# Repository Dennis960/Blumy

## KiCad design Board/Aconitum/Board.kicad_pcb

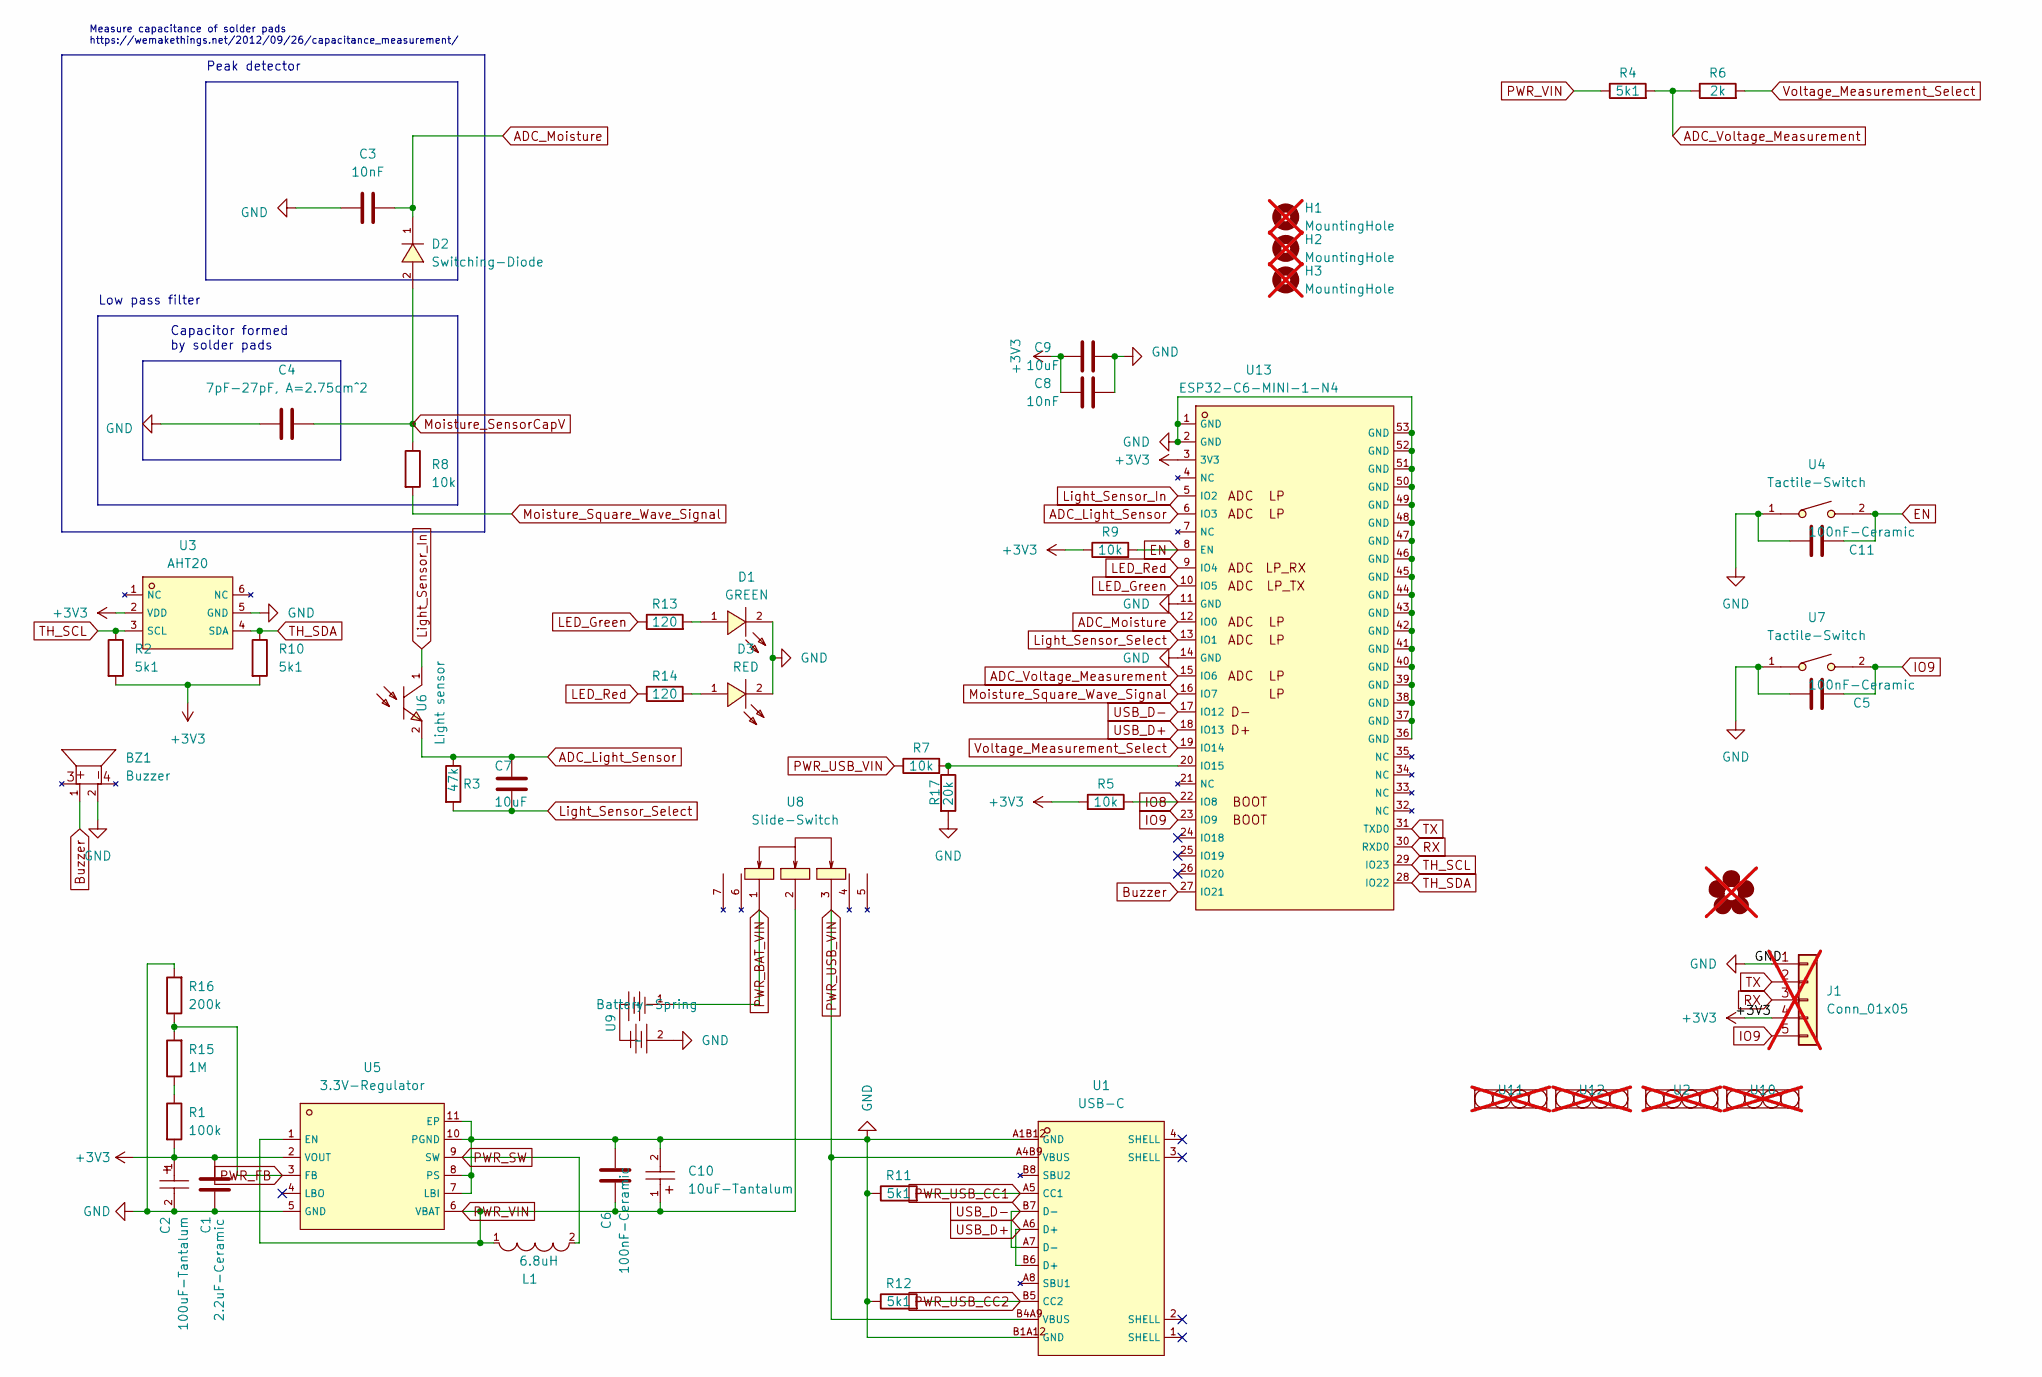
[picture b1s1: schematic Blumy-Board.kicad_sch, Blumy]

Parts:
BZ1: Buzzer; BUZ-SMD_4P-L8.5-W8.5-P8.50-BR; MPN C94599; LCSC C94599
C1: 2.2uF-Ceramic; C_0402_1005Metric; MPN C12530; LCSC C12530
C2: 100uF-Tantalum; CASE-B_3528; MPN C16133; LCSC C16133
C3, C8: 10nF; C_0402_1005Metric; MPN C15195; LCSC C15195
C4: 7pF-27pF, A=2.75cm^2; Sensor-Tip; MPN /
C5, C6, C11: 100nF-Ceramic; C_0402_1005Metric; MPN C1525; LCSC C1525
C7, C9: 10uF; C_0402_1005Metric; MPN C15525; LCSC C15525
C10: 10uF-Tantalum; CAP-SMD_L3.2-W1.6-RD-C7171; MPN C7171; LCSC C7171
D1: GREEN; LED0805-R-RD; MPN C2297; LCSC C2297
D2: Switching-Diode; SOD-123F_L2.7-W1.6-LS3.8-RD; MPN C81598; LCSC C81598
D3: RED; LED0805-R-RD; MPN C84256; LCSC C84256
Flower1: Flower; not fitted
H1, H2, H3: MountingHole; MountingHole_3.2mm_M3; MPN /; not fitted
J1: Conn_01x05; PinHeader_1x05_P2.54mm_Vertical_SMD; MPN /; not fitted
L1: 6.8uH; IND-SMD_L3.5-W3.0; MPN C492260; LCSC C492260
R1: 100k; R_0402_1005Metric; MPN C25741; LCSC C25741
R2, R4, R10, R11, R12: 5k1; R_0402_1005Metric; MPN C25905; LCSC C25905
R3: 47k; R_0402_1005Metric; MPN C25792; LCSC C25792
R5, R7, R8, R9: 10k; R_0402_1005Metric; MPN C25744; LCSC C25744
R6: 2k; R_0402_1005Metric; MPN C4109; LCSC C4109
R13, R14: 120; R_0402_1005Metric; MPN C25079; LCSC C25079
R15: 1M; R_0402_1005Metric; MPN C26083; LCSC C26083
R16: 200k; R_0402_1005Metric; MPN C25764; LCSC C25764
R17: 20k; R_0402_1005Metric; MPN C25765; LCSC C25765
U1: USB-C; USB-C-SMD_G-SWITCH_GT-USB-7010EN; MPN C2997435; LCSC C2997435
U2, U10, U11, U12: MouseBites5mm; MPN /; not fitted
U3: AHT20; SENSOR-SMD-6_AHT20; MPN C2757850; LCSC C2757850
U4, U7: Tactile-Switch; SW-SMD_L3.9-W3.0-P4.45; MPN C720477; LCSC C720477
U5: 3.3V-Regulator; VSON-10_L3.0-W3.0-P0.50-BL-EP_TPS62410DRCR; MPN C71369; LCSC C71369
U6: Light sensor; SENSORS-SMD_ALS-PT19; MPN C146233; LCSC C146233
U8: Slide-Switch; SW-SMD_MK-12C02-G025; MPN C778186; LCSC C778186
U9: Battery-Spring; AAA Battery-spring; MPN /
U13: ESP32-C6-MINI-1-N4; WIFIM-SMD_61P-L16.6-W13.2-P0.80-ESP32-C6-MINI-1-N4; MPN C5736265; LCSC C5736265

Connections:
+3V3: C1.2, C2.1, C8.1, C9.1, J1.4, R1.2, R2.2, R5.2, R9.1, R10.2, U3.2 (VDD), U5.2 (VOUT), U13.3 (3V3)
ADC_Light_Sensor: C7.1, R3.1, U6.2 (E), U13.6 (IO3)
ADC_Moisture: C3.2, D2.1 (K), U13.12 (IO0)
ADC_Voltage_Measurement: R4.2, R6.1, U13.15 (IO6)
Buzzer: BZ1.1 (+), U13.27 (IO21)
EN: C11.1, R9.2, U4.2, U13.8 (EN)
GND: BZ1.2, C1.1, C2.2, C3.1, C4.2, C5.2, C6.2, C8.2, C9.2, C10.2, C11.2, D1.2 (K), D3.2 (-), J1.1, R11.1, R12.1, R16.2, R17.2, U1.A1B12 (GND), U1.B1A12 (GND), U3.5 (GND), U4.1, U5.5 (GND), U5.7 (LBI), U5.8 (PS), U5.10 (PGND), U5.11 (EP), U7.1, U9.2 (-), U13.1 (GND), U13.2 (GND), U13.11 (GND), U13.14 (GND), U13.36 (GND), U13.37 (GND), U13.38 (GND), U13.39 (GND), U13.40 (GND), U13.41 (GND), U13.42 (GND), U13.43 (GND), U13.44 (GND), U13.45 (GND), U13.46 (GND), U13.47 (GND), U13.48 (GND), U13.49 (GND), U13.50 (GND), U13.51 (GND), U13.52 (GND), U13.53 (GND)
IO8: R5.1, U13.22 (IO8)
IO9: C5.1, J1.5, U7.2, U13.23 (IO9)
LED_Green: R13.1, U13.10 (IO5)
LED_Red: R14.1, U13.9 (IO4)
Light_Sensor_In: U6.1 (C), U13.5 (IO2)
Light_Sensor_Select: C7.2, R3.2, U13.13 (IO1)
Moisture_SensorCapV: C4.1, D2.2 (A), R8.1
Moisture_Square_Wave_Signal: R8.2, U13.16 (IO7)
unnamed: D1.1 (A), R13.2
unnamed: D3.1 (+), R14.2
unnamed: R1.1, R15.1
unnamed: R7.2, R17.1, U13.20 (IO15)
PWR_BAT_VIN: U8.1, U9.1 (+)
PWR_FB: R15.2, R16.1, U5.3 (FB)
PWR_SW: L1.2, U5.9 (SW)
PWR_USB_CC1: R11.2, U1.A5 (CC1)
PWR_USB_CC2: R12.2, U1.B5 (CC2)
PWR_USB_VIN: R7.1, U1.A4B9 (VBUS), U1.B4A9 (VBUS), U8.3
PWR_VIN: C6.1, C10.1, L1.1, R4.1, U5.1 (EN), U5.6 (VBAT), U8.2
RX: J1.3, U13.30 (RXD0)
TH_SCL: R2.1, U3.3 (SCL), U13.29 (IO23)
TH_SDA: R10.1, U3.4 (SDA), U13.28 (IO22)
TX: J1.2, U13.31 (TXD0)
USB_D+: U1.A6 (D+), U1.B6 (D+), U13.18 (IO13)
USB_D-: U1.A7 (D-), U1.B7 (D-), U13.17 (IO12)
Voltage_Measurement_Select: R6.2, U13.19 (IO14)

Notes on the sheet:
Capacitor formed by solder pads
Measure capacitance of solder pads https://wemakethings.net/2012/09/26/capacitance_measurement/
Peak detector
Low pass filter

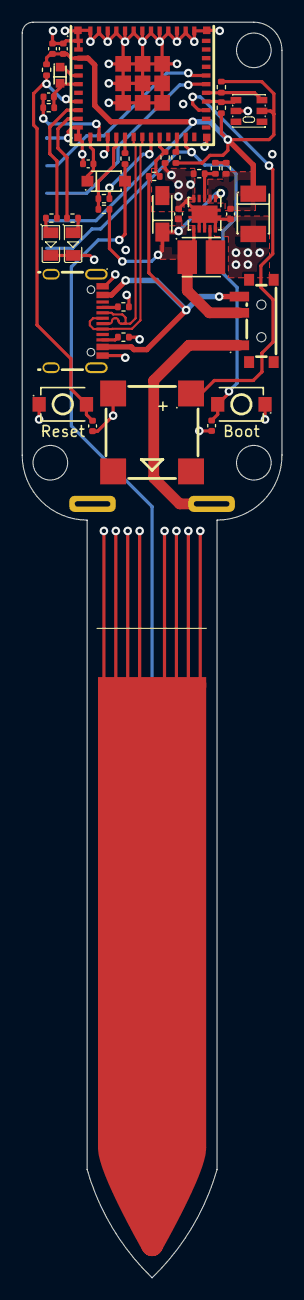
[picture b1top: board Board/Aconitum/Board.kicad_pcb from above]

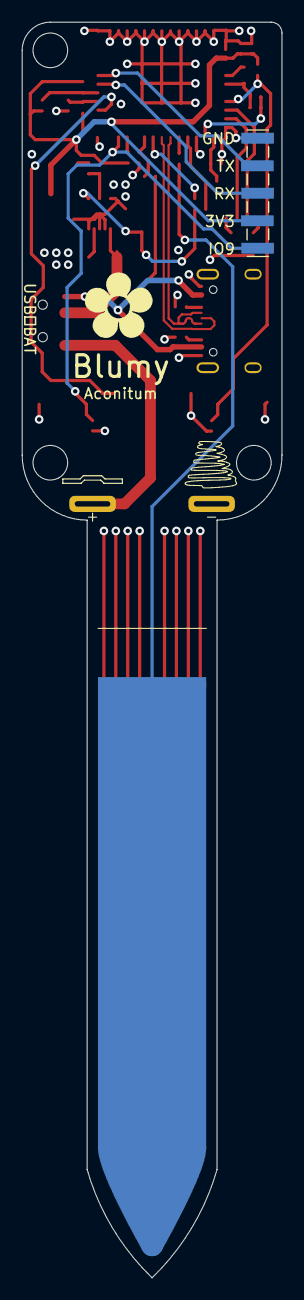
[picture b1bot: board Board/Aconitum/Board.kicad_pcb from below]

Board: 4 copper layers, 24.0 x 116.0 mm, 51 parts (4 on the bottom side), 33 nets.

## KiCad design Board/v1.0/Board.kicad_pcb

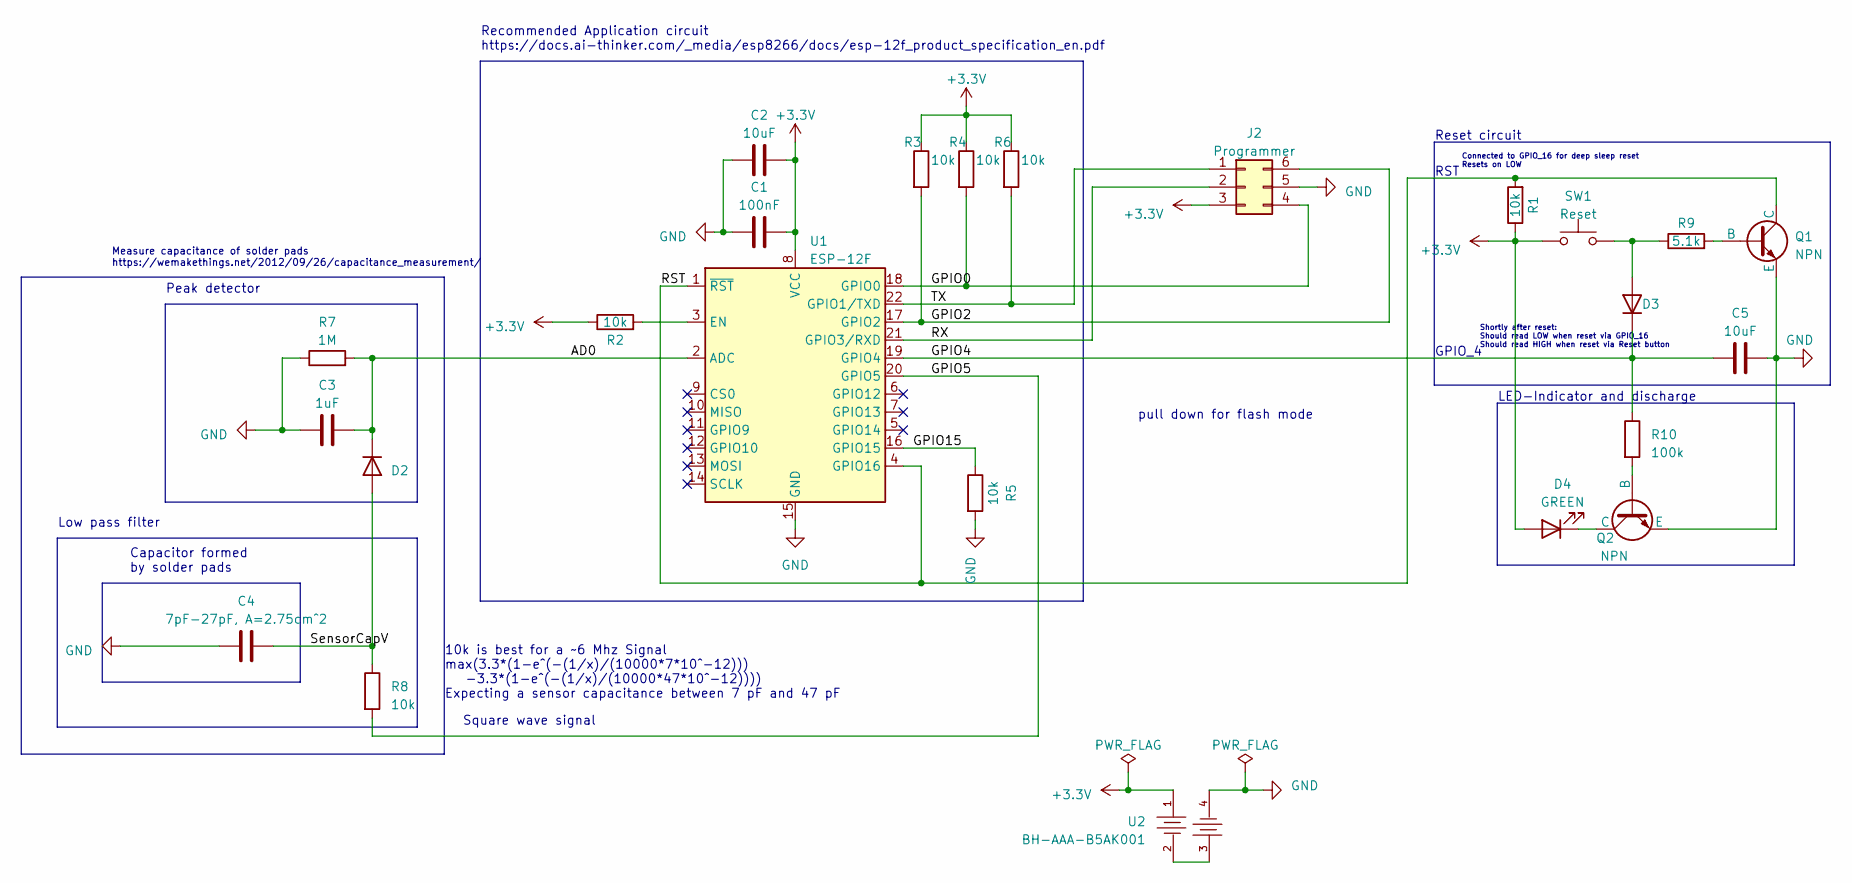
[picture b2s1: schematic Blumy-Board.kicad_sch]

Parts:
C1: 100nF; C_0402_1005Metric; MPN C1525; LCSC C1525
C2, C5: 10uF; C_0402_1005Metric; MPN C15525; LCSC C15525
C3: 1uF; C_0402_1005Metric; MPN C52923; LCSC C52923
C4: 7pF-27pF, A=2.75cm^2
D2, D3: D_SOD-123F; MPN C81598; LCSC C81598
D4: GREEN; LED_0805_2012Metric; MPN C2297; LCSC C2297
J2: Programmer; PinHeader_2x03_P2.54mm_Vertical
Q1, Q2: NPN; SOT-23; MPN C2146; LCSC C2146
R1, R2, R3, R4, R5, R6, R8: 10k; R_0402_1005Metric; MPN C25744; LCSC C25744
R7: 1M; R_0402_1005Metric; MPN C26083; LCSC C26083
R9: 5.1k; R_0402_1005Metric; MPN C25905; LCSC C25905
R10: 100k; R_0402_1005Metric; MPN C25741; LCSC C25741
SW1: Reset; SW_Push_1P1T_XKB_TS-1187A; MPN C318884; LCSC C318884
U1: ESP-12F; ESP-12E; MPN C82891; LCSC C82891
U2: BH-AAA-B5AK001; BAT-SMD_BH-AAA-B5AA001; MPN C964881; LCSC C964881

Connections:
+3.3V: C1.2, C2.2, D4.2 (A), J2.3, R1.1, R2.1, R3.1, R4.1, R6.1, SW1.1, U1.8 (VCC), U2.1 (+)
/AD0: C3.2, D2.1 (K), R7.2, U1.2 (ADC)
/GPIO0: J2.4, R4.2, U1.18 (GPIO0)
/GPIO2: J2.6, R3.2, U1.17 (GPIO2)
/GPIO4: C5.1, D3.1 (K), R10.1, U1.19 (GPIO4)
/GPIO5: R8.2, U1.20 (GPIO5)
/GPIO15: R5.1, U1.16 (GPIO15)
/RST: Q1.1 (C), R1.2, U1.1 (~RST), U1.4 (GPIO16)
/RX: J2.2, U1.21 (GPIO3/RXD)
/SensorCapV: C4.2, D2.2 (A), R8.1
/TX: J2.1, R6.2, U1.22 (GPIO1/TXD)
GND: C1.1, C2.1, C3.1, C4.1, C5.2, J2.5, Q1.3 (E), Q2.3 (E), R5.2, R7.1, U1.15 (GND), U2.4 (-)
unnamed: D3.2 (A), R9.1, SW1.2
unnamed: D4.1 (K), Q2.1 (C)
unnamed: Q1.2 (B), R9.2
unnamed: Q2.2 (B), R10.2
unnamed: R2.2, U1.3 (EN)
unnamed: U2.2 (-), U2.3 (+)

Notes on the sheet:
Capacitor formed by solder pads
Square wave signal
10k is best for a ~6 Mhz Signal max(3.3*(1-e^(-(1/x)/(10000*7*10^-12))) -3.3*(1-e^(-(1/x)/(10000*47*10^-12)))) Expecting a sensor capacitance between 7 pF and 47 pF
Connected to GPIO_16 for deep sleep reset Resets on LOW
Shortly after reset: Should read LOW when reset via GPIO_16 Should read HIGH when reset via Reset button
Recommended Application circuit https://docs.ai-thinker.com/_media/esp8266/docs/esp-12f_product_specification_en.pdf
GPIO_4
Measure capacitance of solder pads https://wemakethings.net/2012/09/26/capacitance_measurement/
Peak detector
RST
pull down for flash mode
Low pass filter
LED-Indicator and discharge
Reset circuit

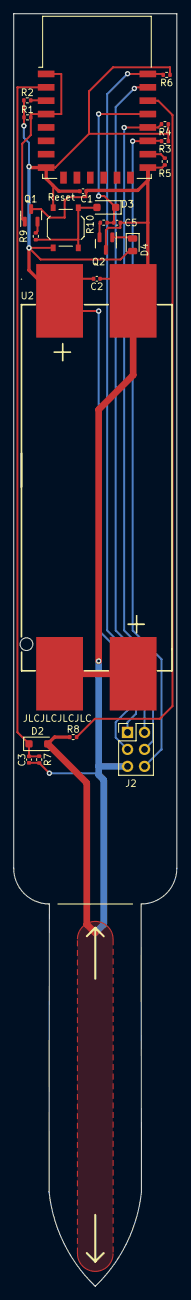
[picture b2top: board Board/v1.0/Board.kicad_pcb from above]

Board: 2 copper layers, 24.4 x 190.2 mm, 23 parts (0 on the bottom side), 18 nets.

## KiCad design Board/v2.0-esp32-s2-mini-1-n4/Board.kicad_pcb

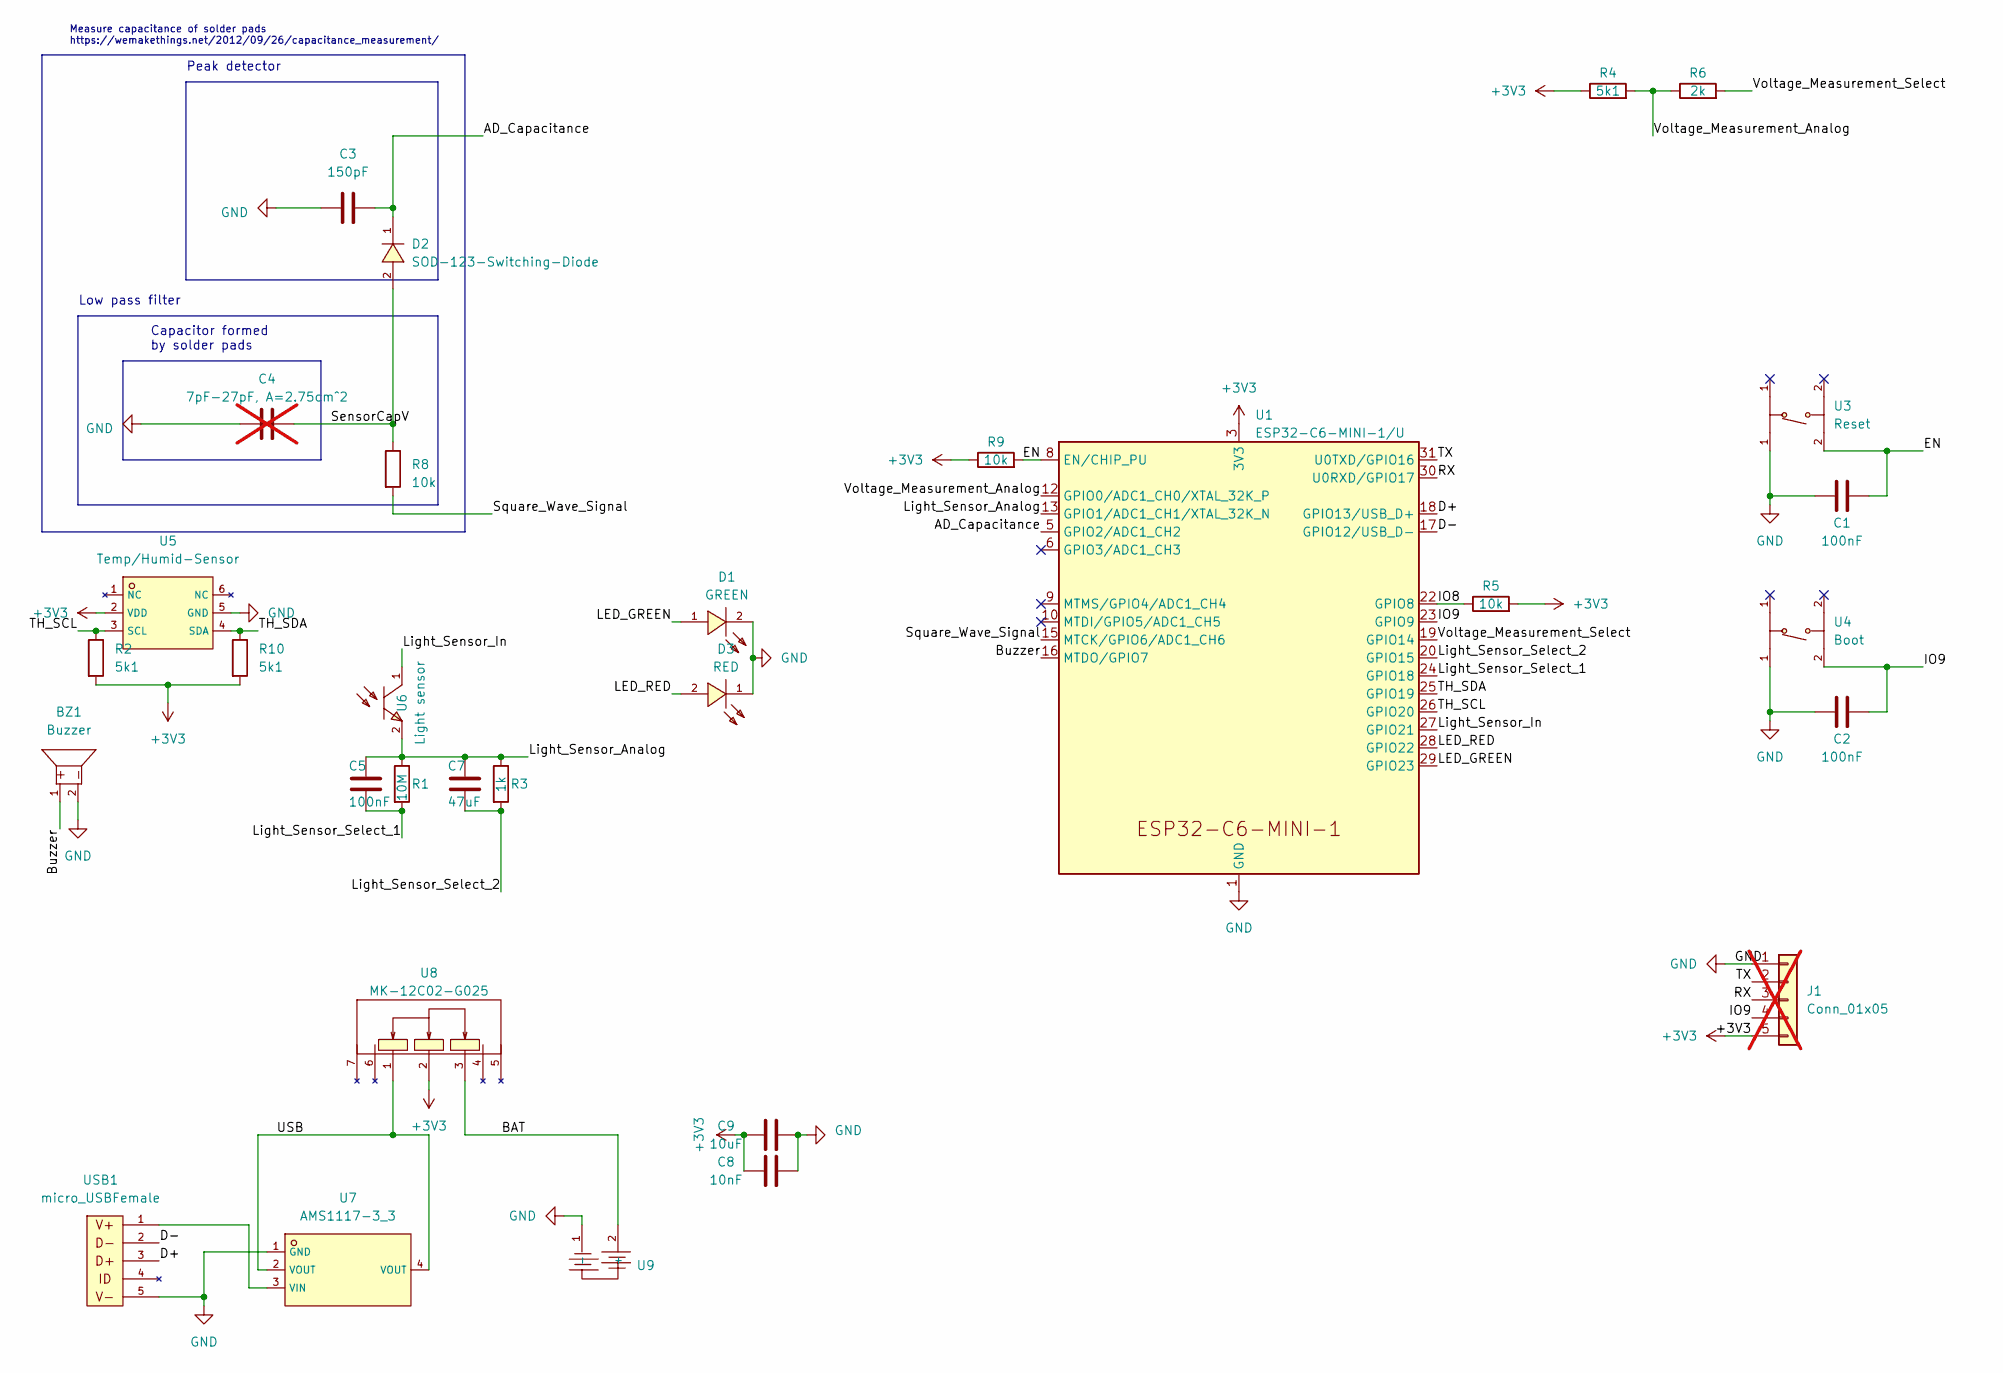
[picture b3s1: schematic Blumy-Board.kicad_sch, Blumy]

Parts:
BZ1: Buzzer; BUZ-SMD_4P-L8.5-W8.5-P8.50-BR; MPN C94599; LCSC C94599
C1, C2, C5: 100nF; C_0402_1005Metric; MPN C1525; LCSC C1525
C3: 150pF; C_0402_1005Metric; MPN C1527; LCSC C1527
C4: 7pF-27pF, A=2.75cm^2; MPN /; LCSC /; not fitted
C7: 47uF; C_0805_2012Metric; MPN C16780; LCSC C16780
C8: 10nF; C_0402_1005Metric; MPN C15195; LCSC C15195
C9: 10uF; C_0402_1005Metric; MPN C15525; LCSC C15525
D1: GREEN; LED0805-GREEN-RD; MPN C2297; LCSC C2297
D2: SOD-123-Switching-Diode; SOD-123F_L2.7-W1.6-LS3.8-RD; MPN C81598; LCSC C81598
D3: RED; LED0805-RD_RED; MPN C84256; LCSC C84256
J1: Conn_01x05; PinHeader_1x05_P2.54mm_Vertical; MPN /; LCSC /; not fitted
R1: 10M; R_0402_1005Metric; MPN C26082; LCSC C26082
R2, R4, R10: 5k1; R_0402_1005Metric; MPN C25905; LCSC C25905
R3: 1k; R_0402_1005Metric; MPN C11702; LCSC C11702
R5, R8, R9: 10k; R_0402_1005Metric; MPN C25744; LCSC C25744
R6: 2k; R_0402_1005Metric; MPN C4109; LCSC C4109
U1: ESP32-C6-MINI-1/U; ESP32-C6-MINI-1; MPN C5736265; LCSC C5736265
U3: Reset; SW_Push_1P1T_XKB_TS-1187A; MPN C318884; LCSC C318884
U4: Boot; SW_Push_1P1T_XKB_TS-1187A; MPN C318884; LCSC C318884
U5: Temp/Humid-Sensor; SENSOR-SMD_L3.0-W3.0-P1.00-BR; MPN C2827328; LCSC C2827328
U6: Light sensor; SENSORS-SMD_ALS-PT19; MPN C146233; LCSC C146233
U7: AMS1117-3_3; SOT-223-3_L6.5-W3.4-P2.30-LS7.0-BR; MPN C6186; LCSC C6186
U8: MK-12C02-G025; SW-SMD_MK-12C02-G025; MPN C778186; LCSC C778186
U9: AAA Battery-spring; MPN /; LCSC /
USB1: micro_USBFemale; MICRO-USB-SMD_5P-P0.65-H-F_C10418; MPN C10418; LCSC C10418

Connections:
+3V3: C8.1, C9.1, J1.5, R2.2, R4.1, R5.2, R9.1, R10.2, U1.3 (3V3), U5.2 (VDD), U8.2
/AD_Capacitance: C3.2, D2.1 (K), U1.5 (GPIO2/ADC1_CH2)
/BAT: U8.3, U9.2 (+)
/Buzzer: BZ1.1 (+), U1.16 (MTDO/GPIO7)
/D+: U1.18 (GPIO13/USB_D+), USB1.3 (D+)
/D-: U1.17 (GPIO12/USB_D-), USB1.2 (D-)
/EN: C1.2, R9.2, U1.8 (EN/CHIP_PU), U3.2 (C)
/IO8: R5.1, U1.22 (GPIO8)
/IO9: C2.2, J1.4, U1.23 (GPIO9), U4.2 (C)
/LED_GREEN: D1.1 (A), U1.29 (GPIO23)
/LED_RED: D3.2 (+), U1.28 (GPIO22)
/Light_Sensor_Analog: C5.1, C7.1, R1.1, R3.1, U1.13 (GPIO1/ADC1_CH1/XTAL_32K_N), U6.2 (E)
/Light_Sensor_In: U1.27 (GPIO21), U6.1 (C)
/Light_Sensor_Select_1: C5.2, R1.2, U1.24 (GPIO18)
/Light_Sensor_Select_2: C7.2, R3.2, U1.20 (GPIO15)
/RX: J1.3, U1.30 (U0RXD/GPIO17)
/SensorCapV: C4.2, D2.2 (A), R8.1
/Square_Wave_Signal: R8.2, U1.15 (MTCK/GPIO6/ADC1_CH6)
/TH_SCL: R2.1, U1.26 (GPIO20), U5.3 (SCL)
/TH_SDA: R10.1, U1.25 (GPIO19), U5.4 (SDA)
/TX: J1.2, U1.31 (U0TXD/GPIO16)
/USB: U7.2 (VOUT), U7.4 (VOUT), U8.1
/Voltage_Measurement_Analog: R4.2, R6.1, U1.12 (GPIO0/ADC1_CH0/XTAL_32K_P)
/Voltage_Measurement_Select: R6.2, U1.19 (GPIO14)
GND: BZ1.2, C1.1, C2.1, C3.1, C4.1, C8.2, C9.2, D1.2 (K), D3.1 (-), J1.1, U1.1 (GND), U1.2 (GND), U1.11 (GND), U1.14 (GND), U1.36 (GND), U1.37 (GND), U1.38 (GND), U1.39 (GND), U1.40 (GND), U1.41 (GND), U1.42 (GND), U1.43 (GND), U1.44 (GND), U1.45 (GND), U1.46 (GND), U1.47 (GND), U1.48 (GND), U1.49 (GND), U1.50 (GND), U1.51 (GND), U1.52 (GND), U1.53 (GND), U3.1 (A), U4.1 (A), U5.5 (GND), U7.1 (GND), U9.1 (-), USB1.5 (V-)
unnamed: U7.3 (VIN), USB1.1 (V+)

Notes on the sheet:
Capacitor formed by solder pads
Measure capacitance of solder pads https://wemakethings.net/2012/09/26/capacitance_measurement/
Peak detector
Low pass filter

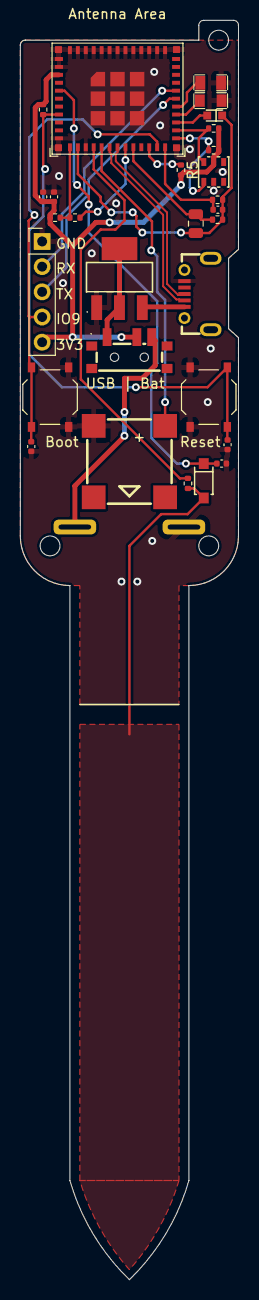
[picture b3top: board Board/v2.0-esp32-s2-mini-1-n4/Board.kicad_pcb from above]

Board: 2 copper layers, 22.0 x 127.0 mm, 30 parts (1 on the bottom side), 26 nets.
